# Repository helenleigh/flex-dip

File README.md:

# Stitch and Glitch

Flex breakout board to make 8 pin DIP, eg LM386 or 555, more easily sewable.

The files used to make the flex DIP breakout board are all above. Here are the slides we'll be using along with some useful links.

### Slides

https://docs.google.com/presentation/d/17nkims0MiGOawY8L7tmUpXSfODSmaSLY-HEM45Ecw_s/edit?usp=sharing

### Instructions

https://docs.google.com/document/d/1NX4CBJA22eWM2ed_EccGdvfCC9_Fk-VF2sbTu3nZUZQ/edit?usp=sharing

### KOBAKANT

https://web.archive.org/web/sitemap/https://www.kobakant.at/DIY/

### Liza Stark

Liza Stark's awesome slides about materials: https://docs.google.com/presentation/d/1vyIxTYRs2cBJge6OkanfHo69W8KlKc8MKb9IgJjPV5M/edit?usp=sharing

https://www.liza-stark.com
https://www.liza-stark.com/projects/zines

### Lara Grant

https://www.instructables.com/How-to-Work-With-Conductive-Fabric/
https://lara-grant.com/

### Rodney Trusty

https://www.youtube.com/watch?v=YerhoMnnhzM
https://www.instagram.com/rodneytrusty/?hl=en

### Nicholas Collins

https://www.nicolascollins.com/handmade.htm

### Events

https://www.electronictextile.camp/faqs
https://etextile-summercamp.org/swatch-exchange/
https://www.pdx.edu/events/ceti-workshop-e-textile-explorations

### Embroidery threads used

https://shop.madeira.co.uk/hc-12-1000m-cone-(high-conductive)_hc12-xxx-xxx.htm
https://www.dmc.com/GB/en-GB/threads-yarns/embroidery-threads

## Making flex PCBs

https://docs.oshpark.com/services/flex/
https://blog.oshpark.com/tag/flex/
https://hackaday.com/2016/05/05/designing-flat-flexible-pcbs/
https://learn.bela.io/tutorials/trill-sensors/designing-a-custom-flex-sensor/

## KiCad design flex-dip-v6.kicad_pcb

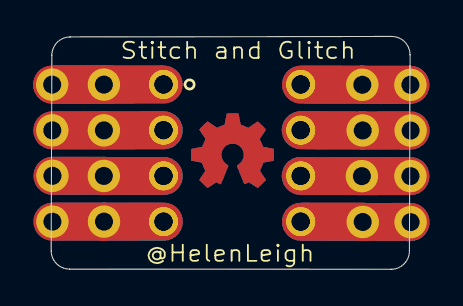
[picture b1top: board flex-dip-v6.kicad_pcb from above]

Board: 2 copper layers, 19.9 x 12.9 mm, 18 parts (0 on the bottom side), 6 nets.

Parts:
J1, J2, J3, J4, J5, J6, J7, J8, J9, J10, J11, J12, J13, J14, J15, J16: Conn_01x01_Female; hole30AWG
U1, U1#2: LM386; DIP-8_W7.62mm

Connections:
+3V3: J2.1, J5.1, J6.1, J7.1, U1.3, U1.6, U1#2.3, U1#2.6
GND: J10.1, J12.1, J13.1, J16.1, U1.2, U1.4, U1#2.2, U1#2.4
unnamed: J1.1, J3.1, U1.7, U1#2.7
unnamed: J4.1, J9.1, U1.5, U1#2.5
unnamed: J11.1, J14.1, U1.8, U1#2.8
unnamed: J8.1, J15.1, U1.1, U1#2.1

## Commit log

2025-03-06 updated silkscreen
    updated silkscreen with current date
